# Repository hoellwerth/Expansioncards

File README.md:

# Expansioncards

A collection of my Expansion Cards for the Framework Laptop

Since I've first seen the Framework Laptop, designing my own Hardware has always fascinated me. I'm working on different Cards ranging from a PD-trigger board over a CAN interface to a TTL converter or even a [dock](https://github.com/Baumistlustig/FrameworkDock)

## Table of Contents

- [CAN](/CAN) A CAN Interface
- [2 USB-C](/2-usb-c) A USB-C Hub card
- [Power output](/power-output) A USB-C PD Trigger card
- [SD-Card](/sd-card) A full-size SD-Card
- [Uart](/uart/) A uart interface card

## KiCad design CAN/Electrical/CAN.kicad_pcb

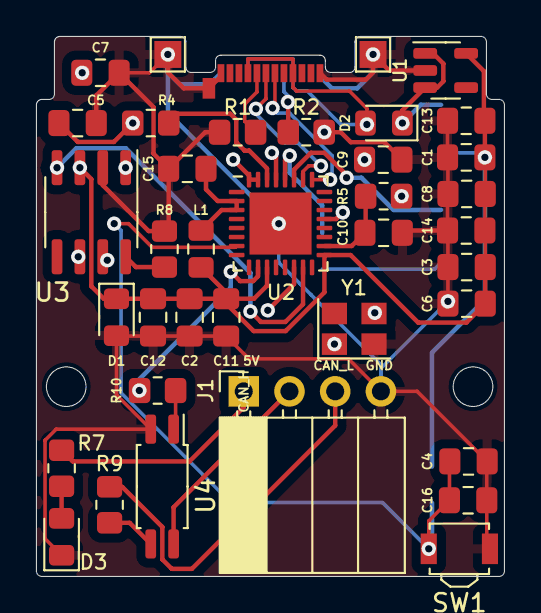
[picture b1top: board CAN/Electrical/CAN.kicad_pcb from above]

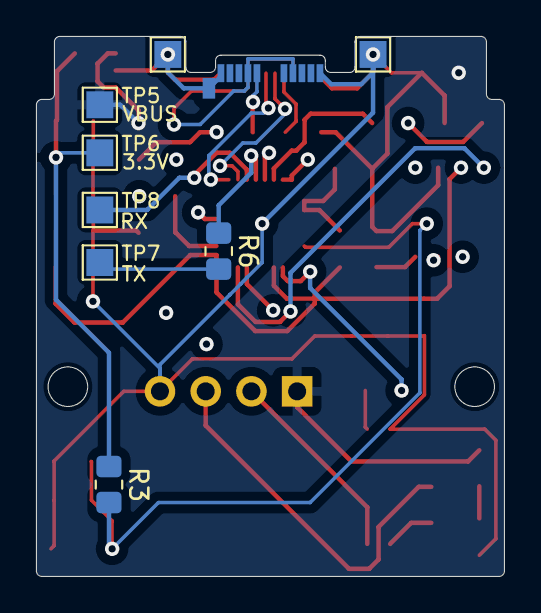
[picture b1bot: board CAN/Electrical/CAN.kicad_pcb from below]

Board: 4 copper layers, 26.0 x 30.0 mm, 48 parts (8 on the bottom side), 27 nets.

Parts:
C1, C7, C8, C13: 10uF; C_0805_2012Metric_Pad1.18x1.45mm_HandSolder
C2, C11, C12, C14, C15, C16: 0.1uF; C_0805_2012Metric_Pad1.18x1.45mm_HandSolder
C3, C4, C10: 1uF; C_0805_2012Metric_Pad1.18x1.45mm_HandSolder
C5, C9: TBD; C_0805_2012Metric_Pad1.18x1.45mm_HandSolder
C6: 10nF; C_0805_2012Metric_Pad1.18x1.45mm_HandSolder
D1: ESD; D_0805_2012Metric_Pad1.15x1.40mm_HandSolder
D2: D_Schottky; D_0805_2012Metric_Pad1.15x1.40mm_HandSolder
D3: LED; LED_0805_2012Metric_Pad1.15x1.40mm_HandSolder
H1, H2: MountingHole; MountingHole_2.2mm_M2
J1: Conn_01x04; PinSocket_1x04_P2.54mm_Horizontal
L1: 2nH; L_0805_2012Metric_Pad1.15x1.40mm_HandSolder
P1: USB_C_Plug_USB2.0; USB_C_Plug_Molex_105444
R1, R2, R7: 5.1k; R_0805_2012Metric_Pad1.20x1.40mm_HandSolder
R3, R5, R8: 10k; R_0805_2012Metric_Pad1.20x1.40mm_HandSolder
R4: 0R; R_0805_2012Metric_Pad1.20x1.40mm_HandSolder
R6: 499R; R_0805_2012Metric_Pad1.20x1.40mm_HandSolder
R9: 120R; R_0805_2012Metric_Pad1.20x1.40mm_HandSolder
R10: 20R; R_0805_2012Metric_Pad1.20x1.40mm_HandSolder
SW1: Reset; SW_SPST_B3U-3000P
TP1, TP2, TP3, TP4: TestPoint; TestPoint_Pad_1.5x1.5mm
TP5: VBUS; TestPoint_Pad_1.5x1.5mm
TP6: 3.3V; TestPoint_Pad_1.5x1.5mm
TP7: TX; TestPoint_Pad_1.5x1.5mm
TP8: RX; TestPoint_Pad_1.5x1.5mm
U1: AP2112K-3.3; SOT-23-5
U2: ESP32-C3; QFN-32-1EP_5x5mm_P0.5mm_EP3.45x3.45mm
U3: SN65HVD230; SOIC-8_3.9x4.9mm_P1.27mm
U4: FODM217D; SOP-4_4.4x2.6mm_P1.27mm
Y1: 40MHz; Crystal_SMD_TXC_7M-4Pin_3.2x2.5mm

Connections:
+3.3V: C1.1, C2.1, C3.1, C6.1, C8.1, C11.1, C12.1, C13.1, C14.1, D1.1 (A1), L1.1, R3.1, TP6.1, U1.5 (VOUT), U2.11 (VDD3P3_RTC), U2.17 (VDD3P3_CPU), U2.31 (VDDA), U2.32 (VDDA), U3.3 (VCC)
/CAN_RX: U2.15 (GPIO9/BOOT), U3.4 (R)
/CAN_TX: U2.14 (GPIO8), U3.1 (D)
/D+: P1.A6 (D+), U2.26 (GPIO19/USB_D+)
/D-: P1.A7 (D-), U2.25 (GPIO18/USB_D-)
/EN: C4.1, C16.2, R3.2, SW1.2, U2.7 (CHIP_EN)
/RXD: TP8.1, U2.27 (U0RXD/GPIO20)
/TERM: R10.1, U2.10 (MTDI/GPIO5/ADC2_CH0)
/TXD: R6.2, TP7.1
/VDD_SPI: C10.1, R5.1, U2.18 (VDD_SPI/GPIO11)
CAN_H: J1.2, U3.7 (CANH), U4.4
CAN_L: J1.3, R9.1, U3.6 (CANL)
GND: C1.2, C2.2, C3.2, C4.2, C5.2, C6.2, C7.2, C8.2, C9.2, C10.2, C11.2, C12.2, C13.2, C14.2, C15.1, C16.1, D1.2 (A2), D3.1 (K), J1.4, P1.A1 (GND), P1.A12 (GND), P1.B1 (GND), P1.B12 (GND), P1.S1 (SHIELD), R1.2, R2.2, R8.1, SW1.1, TP1.1, TP2.1, TP3.1, TP4.1, U1.2 (GND), U2.33 (GND), U3.2 (GND), U4.2, Y1.2
unnamed: C5.1, R4.1, Y1.1
unnamed: C15.2, L1.2, U2.2 (VDD3P3), U2.3 (VDD3P3)
unnamed: D2.2 (A), P1.A4 (VBUS), P1.A9 (VBUS), P1.B4 (VBUS), P1.B9 (VBUS)
unnamed: D3.2 (A), R7.2
unnamed: P1.A5 (CC), R1.1
unnamed: P1.B5 (VCONN), R2.1
unnamed: R9.2, U4.3
unnamed: R10.2, U4.1
unnamed: R5.2, U2.21 (SPICS0/GPIO14)
unnamed: R6.1, U2.28 (U0TXD/GPIO21)
unnamed: C9.1, U2.29 (XTAL_N), Y1.3
unnamed: R4.2, U2.30 (XTAL_P)
unnamed: R8.2, U3.8 (Rs)
VBUS: C7.1, D2.1 (K), J1.1, R7.1, TP5.1, U1.1 (VIN), U1.3 (EN)

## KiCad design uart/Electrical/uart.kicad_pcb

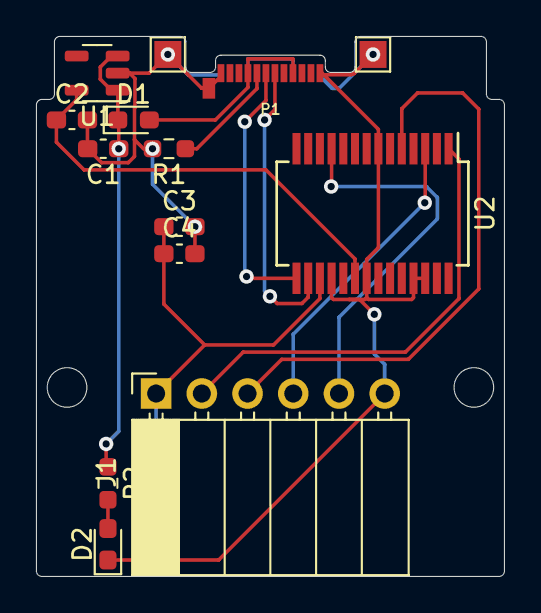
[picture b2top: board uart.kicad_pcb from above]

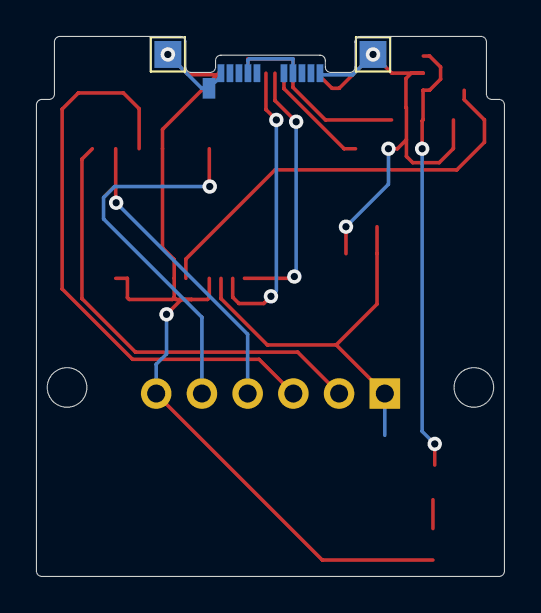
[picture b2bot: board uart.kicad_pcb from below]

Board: 2 copper layers, 26.0 x 30.0 mm, 18 parts (2 on the bottom side), 12 nets.

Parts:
C1, C2, C4: 10uF; C_0603_1608Metric_Pad1.08x0.95mm_HandSolder
C3: 0.1uF; C_0603_1608Metric_Pad1.08x0.95mm_HandSolder
D1: D_Schottky; D_0603_1608Metric_Pad1.05x0.95mm_HandSolder
D2: LED; LED_0603_1608Metric_Pad1.05x0.95mm_HandSolder
H1, H2: MountingHole; MountingHole_2.2mm_M2
J1: Conn_01x06; PinSocket_1x06_P2.54mm_Horizontal
P1: USB_C_Plug_USB2.0; USB_C_Plug_Molex_105444
R1: 5.1k; R_0603_1608Metric_Pad0.98x0.95mm_HandSolder
R2: 1.5k; R_0603_1608Metric_Pad0.98x0.95mm_HandSolder
TP1, TP2, TP3, TP4: TestPoint; TestPoint_Pad_1.5x1.5mm
U1: AP2112K-3.3; SOT-23-5
U2: FT232RL; SSOP-28_5.3x10.2mm_P0.65mm

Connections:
+3V3: C2.1, U1.5 (VOUT), U2.20 (VCC)
/3V3OUT: C3.1, C4.1, J1.1, U2.17 (3V3OUT)
/CTS: J1.5, U2.11 (CTS)
/D+: P1.A6 (D+), U2.15 (USBD+)
/RTS: J1.4, U2.3 (RTS)
/RXD: J1.3, U2.5 (RXD)
/TXD: J1.2, U2.1 (TXD)
GND: C1.2, C2.2, C3.2, C4.2, D2.1 (K), J1.6, P1.A1 (GND), P1.A12 (GND), P1.B1 (GND), P1.B12 (GND), P1.S1 (SHIELD), R1.2, TP1.1, TP2.1, TP3.1, TP4.1, U1.2 (GND), U2.7 (GND), U2.18 (GND), U2.21 (GND), U2.25 (AGND), U2.26 (TEST)
unnamed: D2.2 (A), R2.2
unnamed: P1.A5 (CC), P1.B8, R1.1
VBUS: C1.1, D1.1 (K), R2.1, U1.1 (VIN), U1.3 (EN)
a4: P1.A9 (VBUS), P1.B4 (VBUS), P1.B9 (VBUS), P1.a (VBUS)

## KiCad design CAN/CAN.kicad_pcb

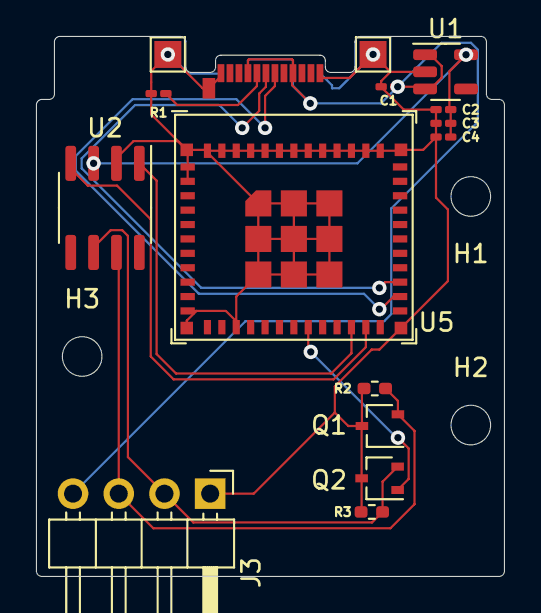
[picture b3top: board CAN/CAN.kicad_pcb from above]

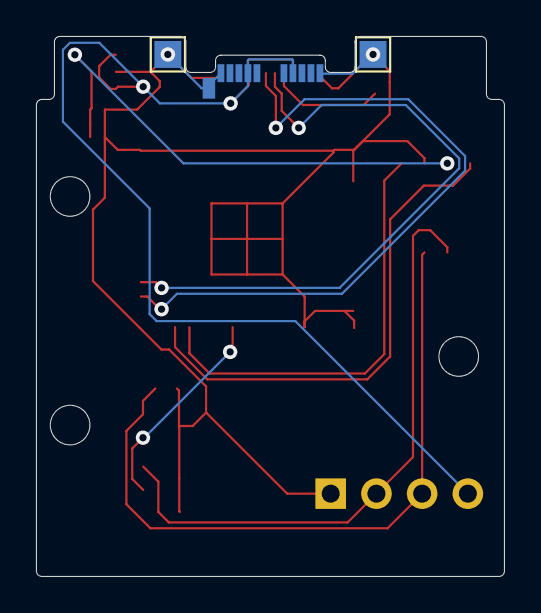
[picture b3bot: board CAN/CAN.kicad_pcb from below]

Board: 2 copper layers, 26.0 x 30.0 mm, 21 parts (2 on the bottom side), 11 nets.

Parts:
C1, C2: 10uF; C_0201_0603Metric_Pad0.64x0.40mm_HandSolder
C3: 22uF; C_0201_0603Metric_Pad0.64x0.40mm_HandSolder
C4: 100nF; C_0201_0603Metric_Pad0.64x0.40mm_HandSolder
H1, H2, H3: MountingHole; MountingHole_2.2mm_M2
J3: Screw_Terminal_01x04; PinHeader_1x04_P2.54mm_Horizontal
P1: USB_C_Plug_USB2.0; USB_C_Plug_Molex_105444
Q1, Q2: BSS214NW; SOT-323_SC-70
R1: 5.1k; R_0201_0603Metric_Pad0.64x0.40mm_HandSolder
R2, R3: 60R; R_0402_1005Metric_Pad0.72x0.64mm_HandSolder
TP1, TP2, TP3, TP4: TestPoint; TestPoint_Pad_1.5x1.5mm
U1: AP2112K-3.3; SOT-23-5
U2: SN65HVD230; SOIC-8_3.9x4.9mm_P1.27mm
U5: ESP32-C3-MINI-1; ESP32-C3-MINI-1U

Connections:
+3V3: C2.1, C3.1, C4.1, U1.5 (VOUT), U2.3 (VCC)
/CAN_RX: U2.4 (R), U5.23 (GPIO9)
/CAN_TX: U2.1 (D), U5.22 (GPIO8)
/D+: P1.A6 (D+), U5.27 (GPIO19/USB_D+)
/D-: P1.A7 (D-), U5.26 (GPIO18/USB_D-)
/TERM: Q1.1 (G), Q2.1 (G), U5.19 (GPIO5/ADC2_CH0)
CAN_H: J3.3, Q1.2 (S), R2.1, U2.7 (CANH)
CAN_L: J3.2, Q2.2 (S), R3.1, U2.6 (CANL)
GND: C1.2, C2.2, C3.2, C4.2, J3.1, P1.A1 (GND), P1.A12 (GND), P1.B1 (GND), P1.B12 (GND), P1.S1 (SHIELD), Q1.3 (D), Q2.3 (D), R1.2, R2.2, R3.2, TP1.1, TP2.1, TP3.1, TP4.1, U1.2 (GND), U2.2 (GND), U5.1 (GND), U5.2 (GND), U5.11 (GND), U5.14 (GND), U5.36 (GND), U5.37 (GND), U5.38 (GND), U5.39 (GND), U5.40 (GND), U5.41 (GND), U5.42 (GND), U5.43 (GND), U5.44 (GND), U5.45 (GND), U5.46 (GND), U5.47 (GND), U5.48 (GND), U5.49 (GND), U5.50 (GND), U5.51 (GND), U5.52 (GND), U5.53 (GND)
unnamed: P1.A5 (CC), R1.1
VBUS: C1.1, J3.4, P1.A4 (VBUS), P1.A9 (VBUS), P1.B4 (VBUS), P1.B9 (VBUS), U1.1 (VIN), U1.3 (EN)

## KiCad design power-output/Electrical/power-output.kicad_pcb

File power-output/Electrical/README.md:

## Power Output Electrical

The KiCad project with schematics and PCBs

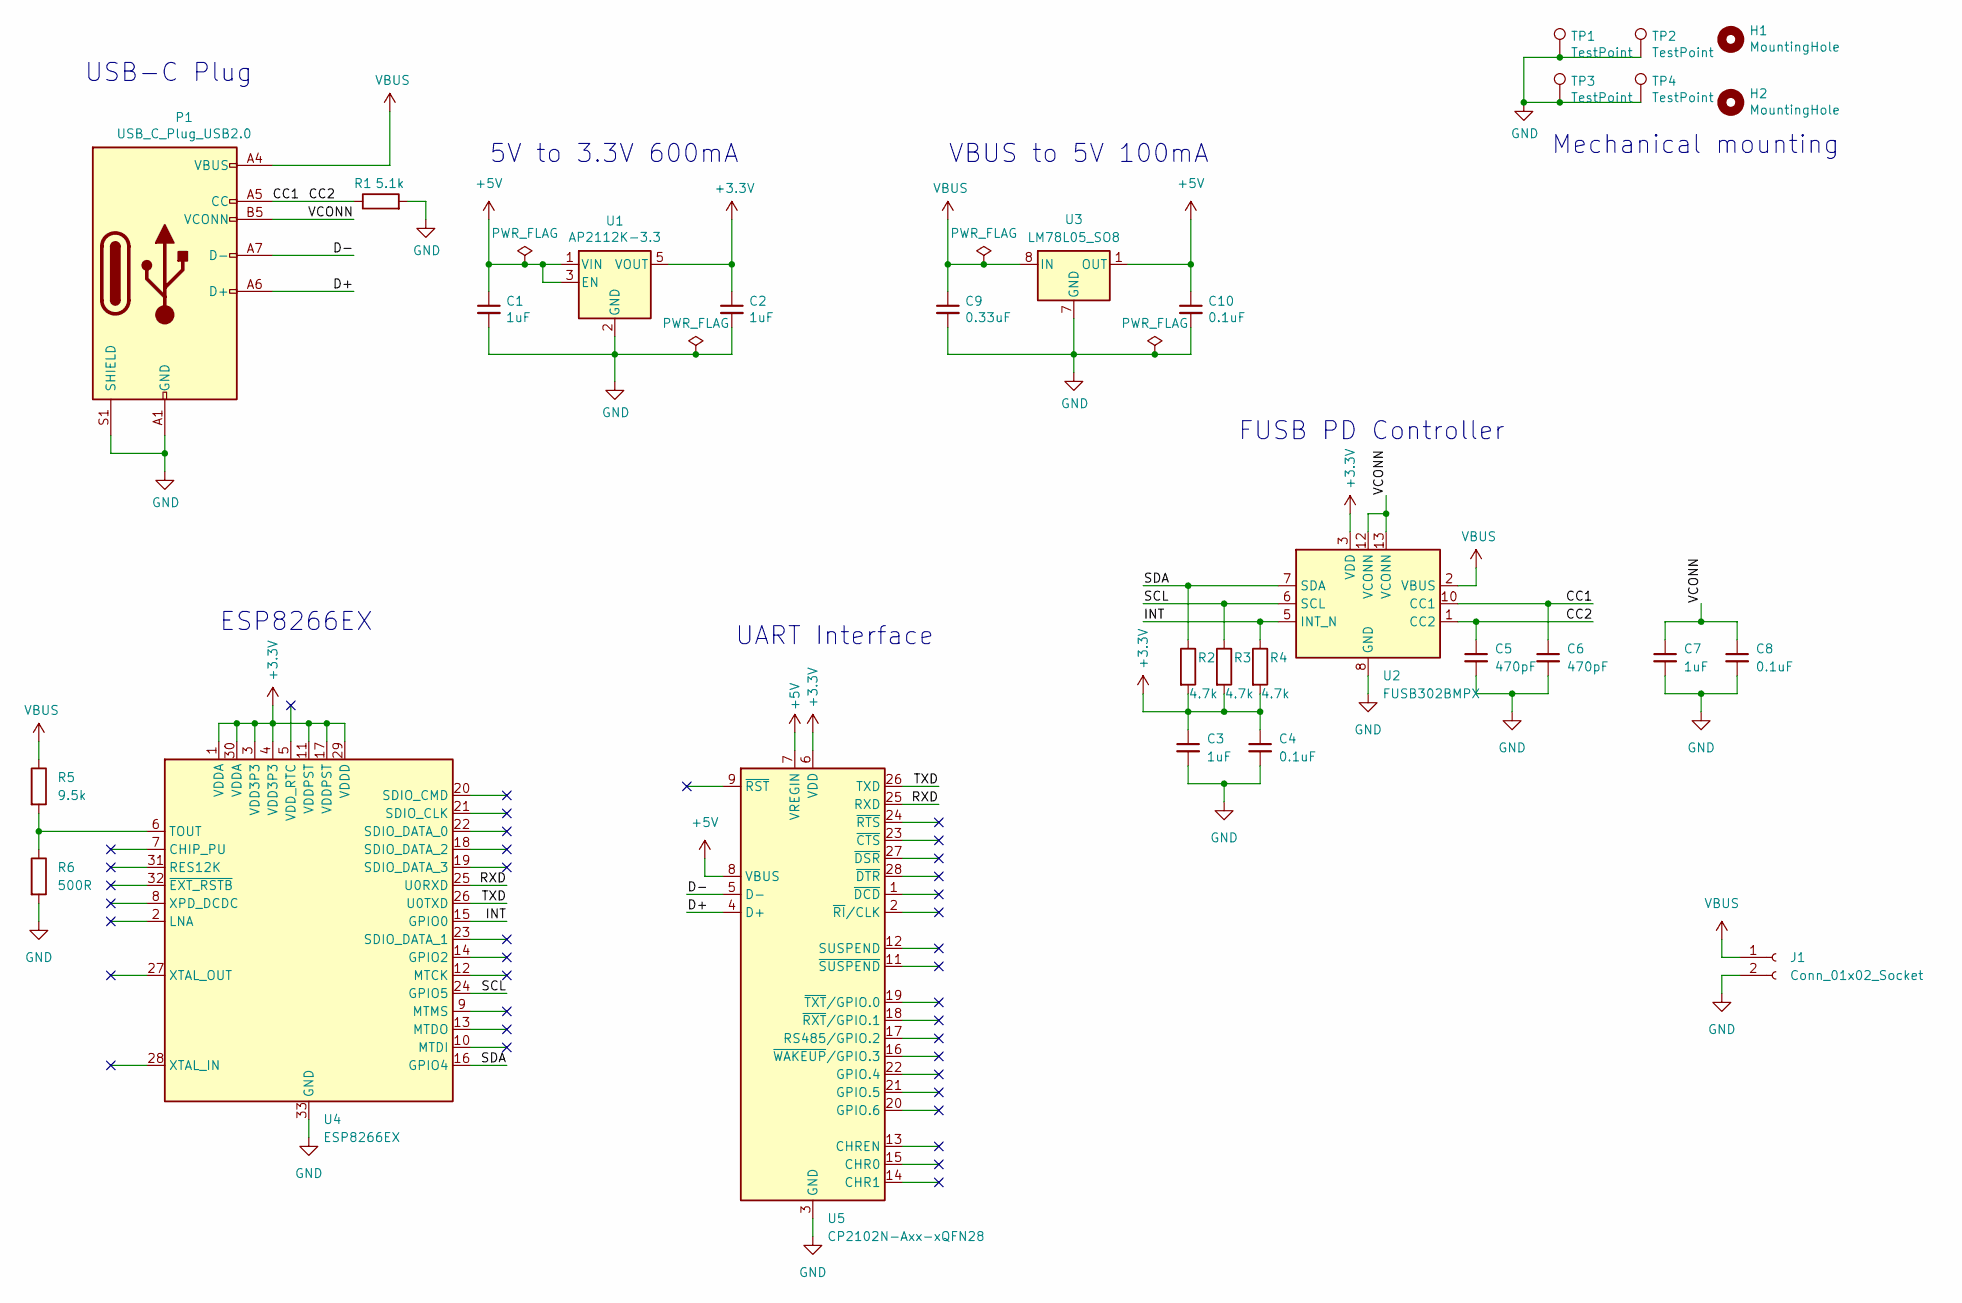
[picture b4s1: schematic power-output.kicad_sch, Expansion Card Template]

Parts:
C1, C2, C3, C7: 1uF; C_0201_0603Metric
C4, C8, C10: 0.1uF; C_0201_0603Metric
C5, C6: 470pF; C_0201_0603Metric
C9: 0.33uF; C_0201_0603Metric
H1, H2: MountingHole; MountingHole_2.2mm_M2
J1: Conn_01x02_Socket; PinSocket_1x02_P2.54mm_Horizontal
P1: USB_C_Plug_USB2.0; USB_C_Plug_Molex_105444
R1: 5.1k; R_0201_0603Metric
R2, R3, R4: 4.7k; R_0201_0603Metric
R5: 9.5k
R6: 500R
TP1, TP2, TP3, TP4: TestPoint; TestPoint_Pad_1.5x1.5mm
U1: AP2112K-3.3; SOT-23-5
U2: FUSB302BMPX; WQFN-14-1EP_2.5x2.5mm_P0.5mm_EP1.45x1.45mm
U3: LM78L05_SO8; SOIC-8_3.9x4.9mm_P1.27mm
U4: ESP8266EX; QFN-32-1EP_5x5mm_P0.5mm_EP3.45x3.45mm
U5: CP2102N-Axx-xQFN28; QFN-28-1EP_5x5mm_P0.5mm_EP3.35x3.35mm

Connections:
+3.3V: C2.1, C3.1, C4.1, R2.2, R3.2, R4.2, U1.5 (VOUT), U2.3 (VDD), U2.4 (VDD), U4.1 (VDDA), U4.3 (VDD3P3), U4.4 (VDD3P3), U4.11 (VDDPST), U4.17 (VDDPST), U4.29 (VDDD), U4.30 (VDDA), U5.6 (VDD)
+5V: C1.1, C10.1, U1.1 (VIN), U1.3 (EN), U3.1 (OUT), U5.7 (VREGIN), U5.8 (VBUS)
/CC1: C5.1, C6.1, P1.A5 (CC), R1.1, U2.1 (CC2), U2.10 (CC1), U2.11 (CC1), U2.14 (CC2)
/D+: P1.A6 (D+), U5.4 (D+)
/D-: P1.A7 (D-), U5.5 (D-)
/INT: R4.1, U2.5 (INT_N), U4.15 (GPIO0)
/RXD: U4.25 (U0RXD), U5.25 (RXD)
/SCL: R3.1, U2.6 (SCL), U4.24 (GPIO5)
/SDA: R2.1, U2.7 (SDA), U4.16 (GPIO4)
/TXD: U4.26 (U0TXD), U5.26 (TXD)
/VCONN: C7.1, C8.1, P1.B5 (VCONN), U2.12 (VCONN), U2.13 (VCONN)
GND: C1.2, C2.2, C3.2, C4.2, C5.2, C6.2, C7.2, C8.2, C9.2, C10.2, J1.2, P1.A1 (GND), P1.A12 (GND), P1.B1 (GND), P1.B12 (GND), P1.S1 (SHIELD), R1.2, R6.2, TP1.1, TP2.1, TP3.1, TP4.1, U1.2 (GND), U2.8 (GND), U2.9 (GND), U2.15 (GND), U3.2 (GND), U3.3 (GND), U3.6 (GND), U3.7 (GND), U4.33 (GND), U5.3 (GND), U5.29 (GND)
unnamed: R5.2, R6.1, U4.6 (TOUT)
VBUS: C9.1, J1.1, P1.A4 (VBUS), P1.A9 (VBUS), P1.B4 (VBUS), P1.B9 (VBUS), R5.1, U2.2 (VBUS), U3.8 (IN)

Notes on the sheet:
ESP8266EX
VBUS to 5V 100mA
5V to 3.3V 600mA
USB-C Plug
Mechanical mounting
FUSB PD Controller
UART Interface

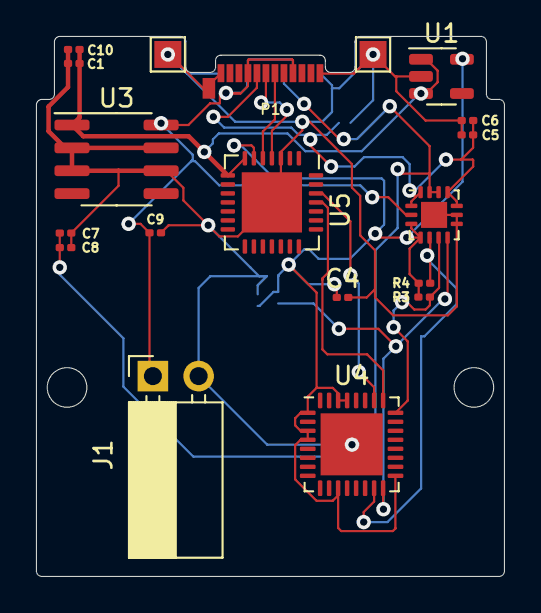
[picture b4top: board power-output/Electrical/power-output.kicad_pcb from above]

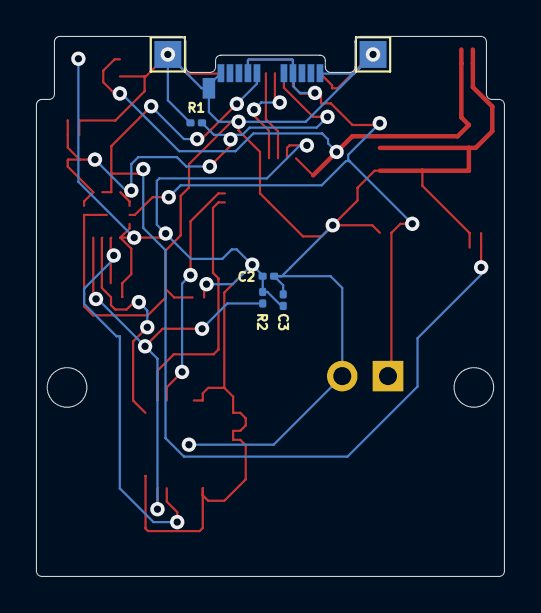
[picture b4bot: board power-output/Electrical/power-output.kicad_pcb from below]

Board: 2 copper layers, 26.0 x 30.0 mm, 27 parts (6 on the bottom side), 13 nets.

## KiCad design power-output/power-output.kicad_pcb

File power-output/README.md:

## Power Output

A USB-C PD Trigger Board which can output a configured voltage (3.3V, 5V, 9V, 12V, 15V, 20V)

## Table of Contents

- [Electrical](/power-output/Electrical) The KiCad project with schemactics and PCBs
- [Software](/power-output/Software) The ArduinoIDE script to controll the board
- [Mechanical](/power-output/Mechanical) Case and other mechancial features

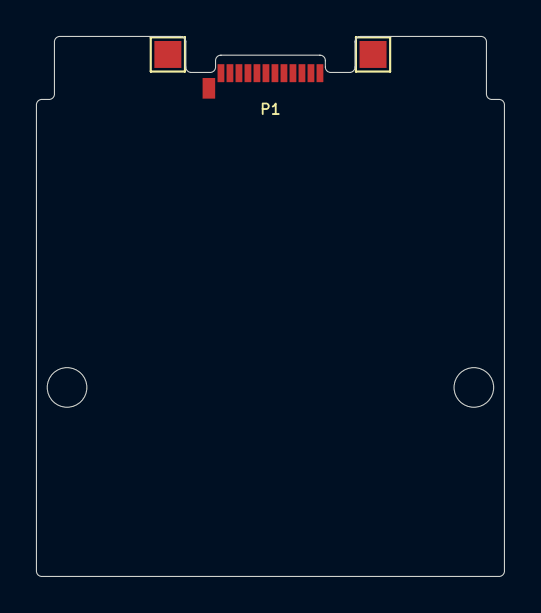
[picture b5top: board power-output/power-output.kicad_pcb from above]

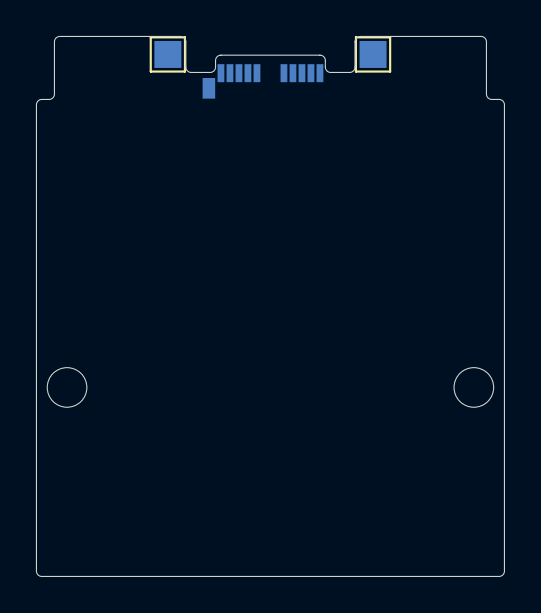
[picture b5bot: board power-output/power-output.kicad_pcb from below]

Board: 2 copper layers, 26.0 x 30.0 mm, 7 parts (2 on the bottom side), 2 nets, no tracks yet.

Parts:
H1, H2: MountingHole; MountingHole_2.2mm_M2
P1: USB_C_Plug_USB2.0; USB_C_Plug_Molex_105444
TP1, TP2, TP3, TP4: TestPoint; TestPoint_Pad_1.5x1.5mm

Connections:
GND: P1.A1 (GND), P1.A12 (GND), P1.B1 (GND), P1.B12 (GND), P1.S1 (SHIELD), TP1.1, TP2.1, TP3.1, TP4.1
VBUS: P1.A4 (VBUS), P1.A9 (VBUS), P1.B4 (VBUS), P1.B9 (VBUS)

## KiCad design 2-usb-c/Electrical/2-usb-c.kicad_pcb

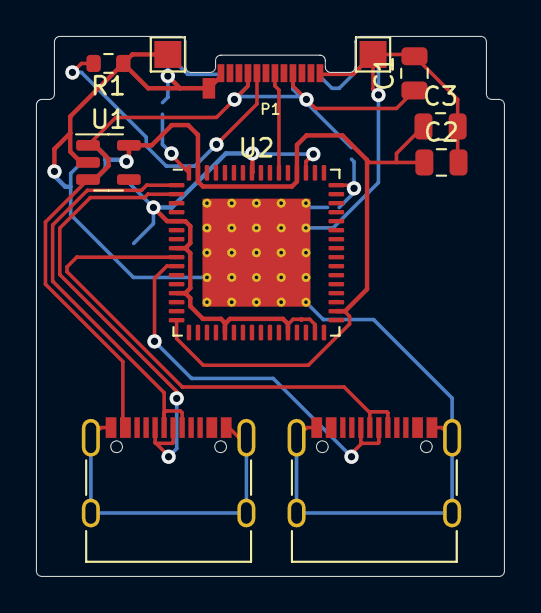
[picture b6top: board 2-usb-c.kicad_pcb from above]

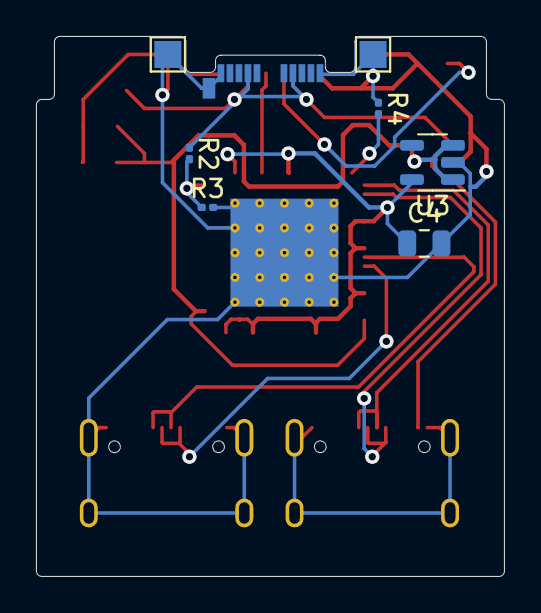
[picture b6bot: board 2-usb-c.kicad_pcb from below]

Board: 2 copper layers, 26.0 x 30.0 mm, 18 parts (7 on the bottom side), 14 nets.

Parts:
C1, C2, C3, C4: 10uF; C_0805_2012Metric
J1, J2: USB_C_Receptacle; USB_C_Receptacle_XKB_U262-16XN-4BVC11
P1: USB_C_Plug_USB2.0; USB_C_Plug_Molex_105444
R1: 5.1k; R_0603_1608Metric
R2: 90.9K; R_0201_0603Metric
R3: 10K; R_0201_0603Metric
R4: 9.53K; R_0201_0603Metric
TP1, TP2, TP3, TP4: TestPoint; TestPoint_Pad_1.5x1.5mm
U1: AP2112K-3.3; SOT-23-5
U2: TUSB8041; QFN-64-1EP_9x9mm_P0.5mm_EP6x6mm_ThermalVias
U3: AP2112K-1.2; SOT-23-5

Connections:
+1V2: C4.1, U2.5 (VDD), U2.8 (VDD), U2.13 (VDD), U2.21 (VDD), U2.28 (VDD), U2.31 (VDD), U2.51 (VDD), U2.57 (VDD), U3.5 (VOUT)
+3V3: C2.1, C3.1, U1.5 (VOUT), U2.16 (VDD33), U2.34 (VDD33), U2.52 (VDD33), U2.63 (VDD33), U3.1 (VIN), U3.3 (EN)
/D1: J1.A6 (D+), J1.B6 (D+), U2.1 (USB_DP_DN1)
/D1-: J1.A7 (D-), J1.B7 (D-), U2.2 (USB_DM_DN1)
/D2: J2.A6 (D+), J2.B6 (D+), U2.9 (USB_DP_DN2)
/D2-: J2.A7 (D-), J2.B7 (D-), U2.10 (USB_DM_DN2)
/D-: P1.A7 (D-), U2.54 (USB_DM_UP)
/SBU1: J1.A8 (SBU1), J2.A8 (SBU1)
/SBU2: J1.B8 (SBU2), J2.B8 (SBU2)
GND: C1.2, C2.2, C3.2, C4.2, J1.A1 (GND), J1.A12 (GND), J1.B1 (GND), J1.B12 (GND), J1.S1 (SHIELD), J2.A1 (GND), J2.A12 (GND), J2.B1 (GND), J2.B12 (GND), J2.S1 (SHIELD), P1.A1 (GND), P1.A12 (GND), P1.B1 (GND), P1.B12 (GND), P1.S1 (SHIELD), R1.2, R3.2, R4.1, TP1.1, TP2.1, TP3.1, TP4.1, U1.2 (GND), U2.65 (VSS), U3.2 (GND)
unnamed: P1.A5 (CC), R1.1
unnamed: R2.2, R3.1, U2.48 (USB_VBUS)
unnamed: R4.2, U2.64 (USB_R1)
VBUS: C1.1, J1.A4 (VBUS), J1.A9 (VBUS), J1.B4 (VBUS), J1.B9 (VBUS), J2.A4 (VBUS), J2.A9 (VBUS), J2.B4 (VBUS), J2.B9 (VBUS), P1.A4 (VBUS), P1.A9 (VBUS), P1.B4 (VBUS), P1.B9 (VBUS), R2.1, U1.1 (VIN), U1.3 (EN)

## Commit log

2023-04-16 Initialized Repository
2023-04-16 Added Template
2023-04-18 Added Mechanical SD-Card
2023-04-18 Added PDF from Framework Forum
2023-04-20 Added Electrical Project
2023-04-20 Added SD Reader Housing
2023-04-20 Removed ~ExpansionCard.stl
2023-04-21 Added Electrical 2usbc project
2023-04-21 Added 2usbc Schematic
2023-04-21 Added PCB
2023-04-21 Added PRL
2023-04-23 Added SD Card Reader Mechanical Housing Top
2023-04-23 Added UART Project
2023-04-23 Added UART Schematic
2023-04-24 Updated uart project
2023-04-24 Updated uart schematic
2023-04-25 Added uart PCB
2023-04-27 Updated uart PCB
2023-04-27 Updated SD Card Housing Top
2023-04-27 Added 2-usb-c.pdf
2023-06-14 Added Power Output project
2023-06-14 Added Power Output schematic
2023-06-14 Added Power Output pcb
2023-06-20 Create LICENSE
2023-07-01 Added FUSB302BMPX
2023-07-02 Replaced ESP8266 with 8266EX
2023-07-02 Added UART Interface
2023-07-02 Cleaned up Schematics
2023-07-02 Labeled everything in schmatic
2023-07-02 Updated KiCad Project
2023-07-02 Updated Schematic
2023-07-02 Moved into Electrical Folder
2023-07-02 Added Software Fodler
2023-07-02 Moved into usb-c demo folder
2023-07-03 Added Pin Header
2023-07-03 Added Header to PCB
2023-07-10 Cleaned Up power-output
2023-07-10 Added Connector socket
2023-07-10 Cleared Up power-output project
2023-07-10 Added uart backups
2023-07-10 Added Raytraced View of PCB design
2023-07-10 Rename kicad.yml to kibot.yml
2023-07-29 Added gerber files
2023-07-29 Added Backups
2023-07-29 Added BOM
2023-07-29 Cleared power-output project
2023-07-29 Added potential divider
2023-08-09 Initialized CAN project
2023-08-09 Added CAN schematic
2023-08-09 Added CAN backups
2023-08-09 Added ESP32 C3
2023-08-09 Added SN65HVD230 Transceiver
2023-08-09 Added 16MB flash for esp32
2023-08-09 Added external connector
2023-08-09 Added Power Cap
2023-08-09 Added NeoPixel LED
2023-08-09 Added QWiiC Connector
2023-08-09 Reorder Schematic
2023-08-10 Replaced ESP32-C3 with ESP32-C3-MINI-1-U
    Removed external Flash
2023-08-10 Updated PCB
2023-08-10 Added optional Termination resistor
    Two 60R betweeen CAN_L & CAN_H
    Two Mosfets to (de)activate the resistor software side
2023-08-11 Renamed to CAN...
2023-08-11 Removed UART Pins
2023-08-11 Added FSUB PDcontroller
2023-08-11 Removed Neopixel LED & QWIIC Connector
2023-08-11 Removed PD
2023-08-12 Cleaned Schematic
2023-08-12 Updated Project
2023-08-12 Added Schematic PDF
2023-08-12 Added PCB PDF
2023-08-12 Moved KiCad project int o'Electrical'
2023-08-12 Added README.md
2023-08-12 Added Electrical/README.md
2023-08-13 Replaced Footprints
2023-08-13 Fixed S
2023-08-14 Replaced Screw terminal with pin socket
2023-08-14 Updated board view
2023-08-14 Updated Schamtic PDF
2023-08-14 Updated PCB PDF
2023-08-14 Added 'Mechanical' folder
2023-08-18 Added 3d models
2023-10-26 Updated Backups
2023-10-26 Updated Schematic
    Added Volatage output Selection
    Added PullUp resistor & PullDown capacitor to EN
    Added PullUp resistor to GPIO2
    Updated Power cap capacitors
    Added reset button
    Changed Tespoints 7 & 8 to TX and RX
2023-10-26 Updated Board
    Added Ground Plane and power plane
    Updated PCB from Schematic
    Changed to 4 layers
2023-10-26 Replaced photo of board
2023-10-30 Updated board
2023-10-30 Overworked structure
2023-11-01 Added 3d Files
2023-11-15 Added Resistor to protect optocoppler diode
2023-11-16 Added Production output
2023-11-16 Updated board Image
2023-11-16 Updated interactive BOM
2024-02-13 Replaced ESP32 Moduole with ESP32-C3

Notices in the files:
2-usb-c/Electrical/2-usb-c.kicad_pcb:
This work is licensed under a Creative Commons Attribution 4.0 International License
